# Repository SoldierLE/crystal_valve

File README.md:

# 项目说明

​	本项目以学习为目的，主要针对模拟电路设计进行学习。参考的书籍为铃木雅臣的《晶体管电路设计》。

​	本项目将会选取书本中每个章节较为重要的几个实用电路进行PCB制作及测试。

## 文件路径说明

- 01Doc

​- books

2.设计资料

​		此处存放的是学习心得以及每个章节的PCB文件，工具采用开源KICAD，摆脱版权烦恼。

3.测试资料

​		此处将会存放PCB打板回来后的电路实测数据。

4.生产资料

​		此处主要会将最后输出的BOM表和Gerber文件发布于此。并且会做一些生产过程中的问题记录。

​		需要打板的，我尽量将每次的板子都做成100mm*100mm之内的， 以便嘉立创5元打板。

## 当前进度

2020-12-18第二章放大电路------更新至PCB版初版

​		
2025-6-24学习使用vscode进行更新，并更改文件目录，准备之后都用立创EDA

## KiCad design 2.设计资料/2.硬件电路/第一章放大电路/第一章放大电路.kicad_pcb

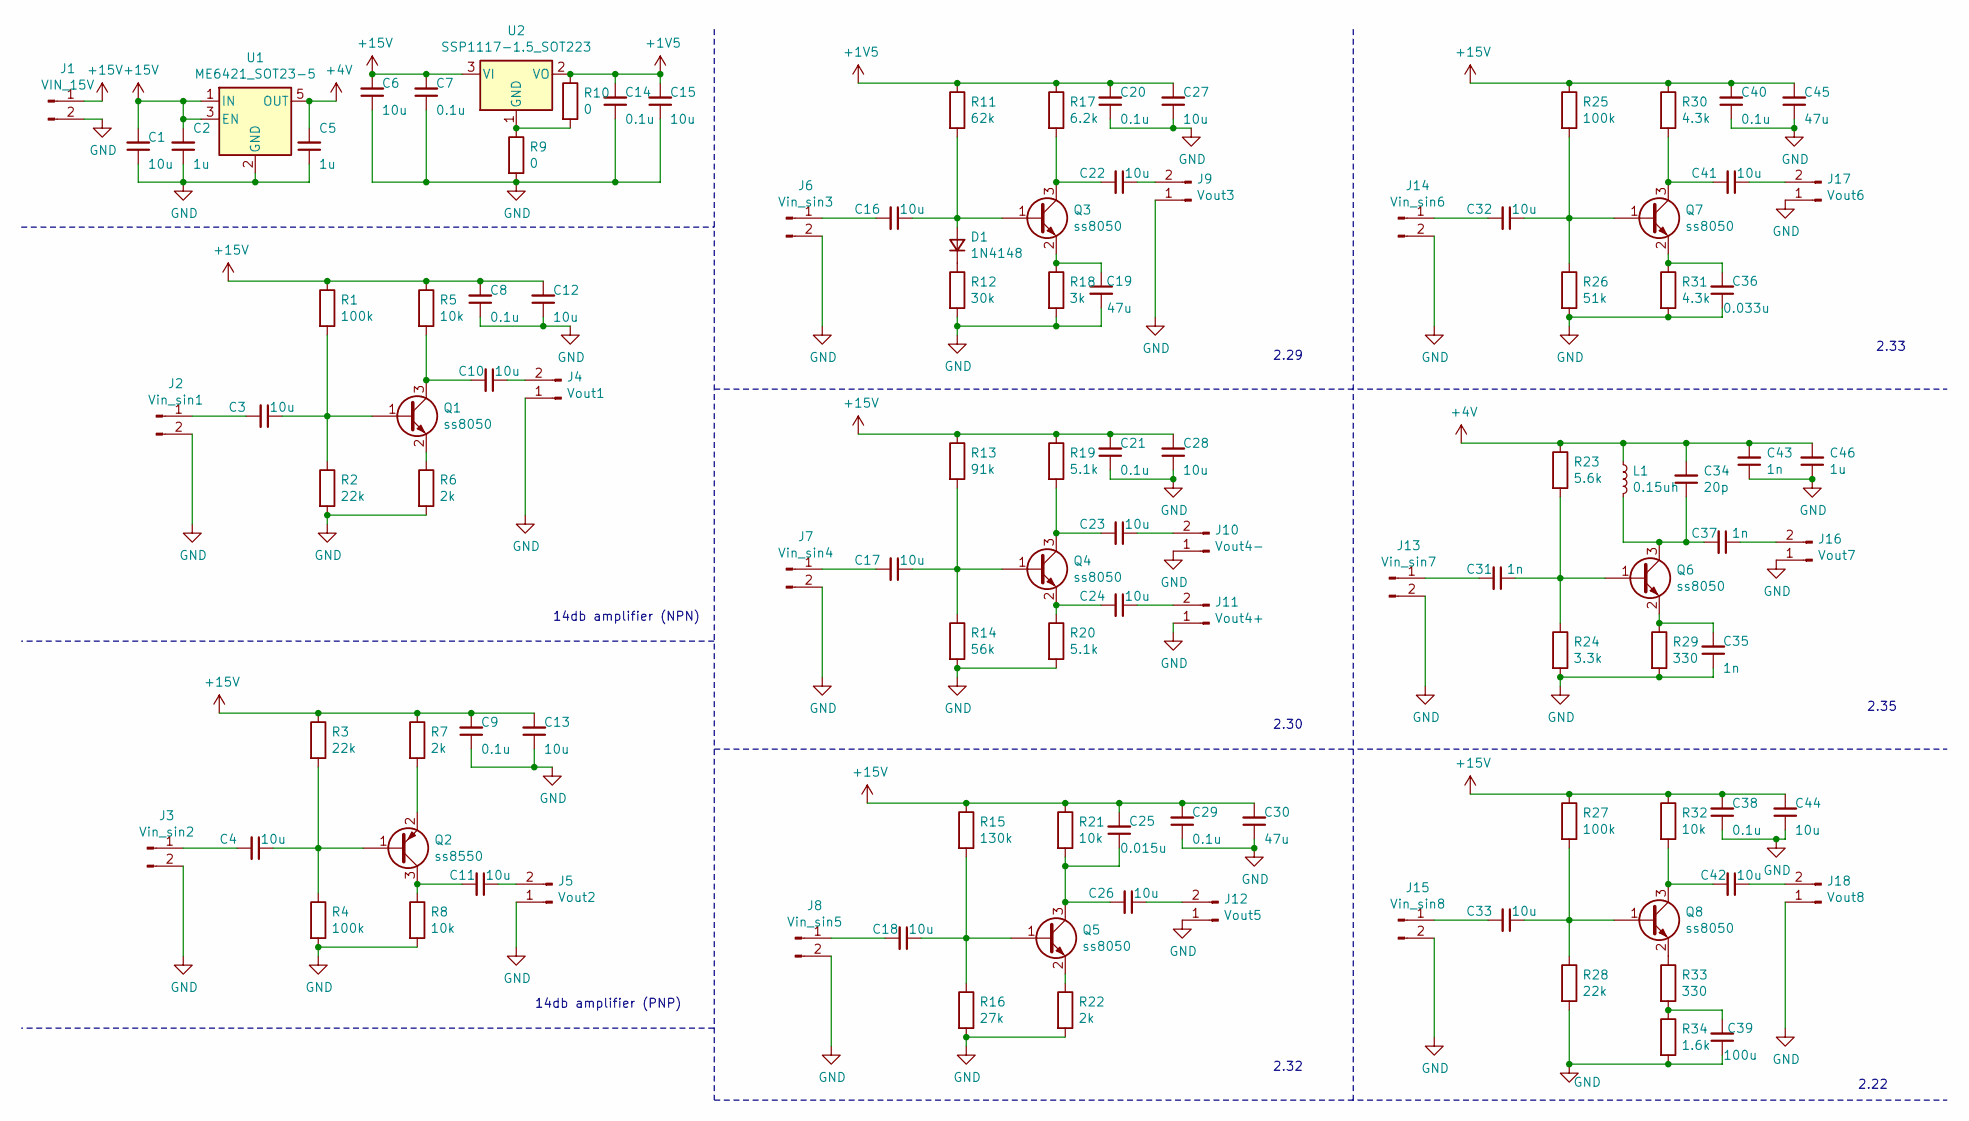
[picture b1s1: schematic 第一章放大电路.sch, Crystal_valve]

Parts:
C1, C3, C4, C6, C10, C11, C12, C13, C15, C16, C17, C18, C22, C23, C24, C26, C27, C28, C32, C33, C41, C42, C44: 10u; C_0603_1608Metric_Pad1.05x0.95mm_HandSolder
C2, C5, C46: 1u; C_0603_1608Metric_Pad1.05x0.95mm_HandSolder
C7, C8, C9, C14, C20, C21, C29, C38, C40: 0.1u; C_0603_1608Metric_Pad1.05x0.95mm_HandSolder
C19, C30, C45: 47u; C_0603_1608Metric_Pad1.05x0.95mm_HandSolder
C25: 0.015u; C_0603_1608Metric_Pad1.05x0.95mm_HandSolder
C31, C35, C37, C43: 1n; C_0603_1608Metric_Pad1.05x0.95mm_HandSolder
C34: 20p; C_0603_1608Metric_Pad1.05x0.95mm_HandSolder
C36: 0.033u; C_0603_1608Metric_Pad1.05x0.95mm_HandSolder
C39: 100u; C_0603_1608Metric_Pad1.05x0.95mm_HandSolder
D1: 1N4148; D_0603_1608Metric_Pad1.05x0.95mm_HandSolder
J1: VIN_15V; PinHeader_1x02_P2.54mm_Vertical
J2: Vin_sin1; PinHeader_1x02_P2.54mm_Vertical
J3: Vin_sin2; PinHeader_1x02_P2.54mm_Vertical
J4: Vout1; PinHeader_1x02_P2.54mm_Vertical
J5: Vout2; PinHeader_1x02_P2.54mm_Vertical
J6: Vin_sin3; PinHeader_1x02_P2.54mm_Vertical
J7: Vin_sin4; PinHeader_1x02_P2.54mm_Vertical
J8: Vin_sin5; PinHeader_1x02_P2.54mm_Vertical
J9: Vout3; PinHeader_1x02_P2.54mm_Vertical
J10: Vout4-; PinHeader_1x02_P2.54mm_Vertical
J11: Vout4+; PinHeader_1x02_P2.54mm_Vertical
J12: Vout5; PinHeader_1x02_P2.54mm_Vertical
J13: Vin_sin7; PinHeader_1x02_P2.54mm_Vertical
J14: Vin_sin6; PinHeader_1x02_P2.54mm_Vertical
J15: Vin_sin8; PinHeader_1x02_P2.54mm_Vertical
J16: Vout7; PinHeader_1x02_P2.54mm_Vertical
J17: Vout6; PinHeader_1x02_P2.54mm_Vertical
J18: Vout8; PinHeader_1x02_P2.54mm_Vertical
L1: 0.15uh; L_0603_1608Metric_Pad1.05x0.95mm_HandSolder
Q1, Q3, Q4, Q5, Q6, Q7, Q8: ss8050; SOT-23
Q2: ss8550; SOT-23
R1, R4, R25, R27: 100k; R_0603_1608Metric_Pad1.05x0.95mm_HandSolder
R2, R3, R28: 22k; R_0603_1608Metric_Pad1.05x0.95mm_HandSolder
R5, R8, R21, R32: 10k; R_0603_1608Metric_Pad1.05x0.95mm_HandSolder
R6, R7, R22: 2k; R_0603_1608Metric_Pad1.05x0.95mm_HandSolder
R9, R10: 0; R_0603_1608Metric_Pad1.05x0.95mm_HandSolder
R11: 62k; R_0603_1608Metric_Pad1.05x0.95mm_HandSolder
R12: 30k; R_0603_1608Metric_Pad1.05x0.95mm_HandSolder
R13: 91k; R_0603_1608Metric_Pad1.05x0.95mm_HandSolder
R14: 56k; R_0603_1608Metric_Pad1.05x0.95mm_HandSolder
R15: 130k; R_0603_1608Metric_Pad1.05x0.95mm_HandSolder
R16: 27k; R_0603_1608Metric_Pad1.05x0.95mm_HandSolder
R17: 6.2k; R_0603_1608Metric_Pad1.05x0.95mm_HandSolder
R18: 3k; R_0603_1608Metric_Pad1.05x0.95mm_HandSolder
R19, R20: 5.1k; R_0603_1608Metric_Pad1.05x0.95mm_HandSolder
R23: 5.6k; R_0603_1608Metric_Pad1.05x0.95mm_HandSolder
R24: 3.3k; R_0603_1608Metric_Pad1.05x0.95mm_HandSolder
R26: 51k; R_0603_1608Metric_Pad1.05x0.95mm_HandSolder
R29, R33: 330; R_0603_1608Metric_Pad1.05x0.95mm_HandSolder
R30, R31: 4.3k; R_0603_1608Metric_Pad1.05x0.95mm_HandSolder
R34: 1.6k; R_0603_1608Metric_Pad1.05x0.95mm_HandSolder
U1: ME6421_SOT23-5; SOT-23-5
U2: SSP1117-1.5_SOT223; SOT-223-3_TabPin2

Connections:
+1V5: C14.2, C15.2, C20.2, C27.2, R10.1, R11.1, R17.1, U2.2 (VO)
+4V: C5.2, C34.2, C43.2, C46.2, L1.1, R23.1, U1.5 (OUT)
+15V: C1.2, C2.2, C6.2, C7.2, C8.2, C9.2, C12.2, C13.2, C21.2, C25.2, C28.2, C29.2, C30.2, C38.2, C40.2, C44.2, C45.2, J1.1, R1.1, R3.1, R5.1, R7.1, R13.1, R15.1, R19.1, R21.1, R25.1, R27.1, R30.1, R32.1, U1.1 (IN), U1.3 (EN), U2.3 (VI)
GND: C1.1, C2.1, C5.1, C6.1, C7.1, C8.1, C9.1, C12.1, C13.1, C14.1, C15.1, C19.2, C20.1, C21.1, C27.1, C28.1, C29.1, C30.1, C35.1, C36.1, C38.1, C39.1, C40.1, C43.1, C44.1, C45.1, C46.1, J1.2, J2.2, J3.2, J4.1, J5.1, J6.2, J7.2, J8.2, J9.1, J10.1, J11.1, J12.1, J13.2, J14.2, J15.2, J16.1, J17.1, J18.1, R2.2, R4.2, R6.2, R8.2, R9.2, R12.2, R14.2, R16.2, R18.2, R20.2, R22.2, R24.2, R26.2, R28.2, R29.2, R31.2, R34.2, U1.2 (GND)
unnamed: C3.1, Q1.1 (B), R1.2, R2.1
unnamed: C3.2, J2.1
unnamed: C4.1, Q2.1 (B), R3.2, R4.1
unnamed: C4.2, J3.1
unnamed: C10.1, J4.2
unnamed: C10.2, Q1.3 (C), R5.2
unnamed: C11.1, J5.2
unnamed: C11.2, Q2.3 (C), R8.1
unnamed: C16.1, D1.2 (A), Q3.1 (B), R11.2
unnamed: C16.2, J6.1
unnamed: C17.1, Q4.1 (B), R13.2, R14.1
unnamed: C17.2, J7.1
unnamed: C18.1, Q5.1 (B), R15.2, R16.1
unnamed: C18.2, J8.1
unnamed: C19.1, Q3.2 (E), R18.1
unnamed: C22.1, J9.2
unnamed: C22.2, Q3.3 (C), R17.2
unnamed: C23.1, J10.2
unnamed: C23.2, Q4.3 (C), R19.2
unnamed: C24.1, J11.2
unnamed: C24.2, Q4.2 (E), R20.1
unnamed: C25.1, C26.2, Q5.3 (C), R21.2
unnamed: C26.1, J12.2
unnamed: C31.1, Q6.1 (B), R23.2, R24.1
unnamed: C31.2, J13.1
unnamed: C32.1, Q7.1 (B), R25.2, R26.1
unnamed: C32.2, J14.1
unnamed: C33.1, Q8.1 (B), R27.2, R28.1
unnamed: C33.2, J15.1
unnamed: C34.1, C37.2, L1.2, Q6.3 (C)
unnamed: C35.2, Q6.2 (E), R29.1
unnamed: C36.2, Q7.2 (E), R31.1
unnamed: C37.1, J16.2
unnamed: C39.2, R33.2, R34.1
unnamed: C41.1, J17.2
unnamed: C41.2, Q7.3 (C), R30.2
unnamed: C42.1, J18.2
unnamed: C42.2, Q8.3 (C), R32.2
unnamed: D1.1 (K), R12.1
unnamed: Q1.2 (E), R6.1
unnamed: Q2.2 (E), R7.2
unnamed: Q5.2 (E), R22.1
unnamed: Q8.2 (E), R33.1
unnamed: R9.1, R10.2, U2.1 (GND)

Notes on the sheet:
14db amplifier (NPN)
14db amplifier (PNP)
2.32
2.30
2.29
2.33
2.35
2.22

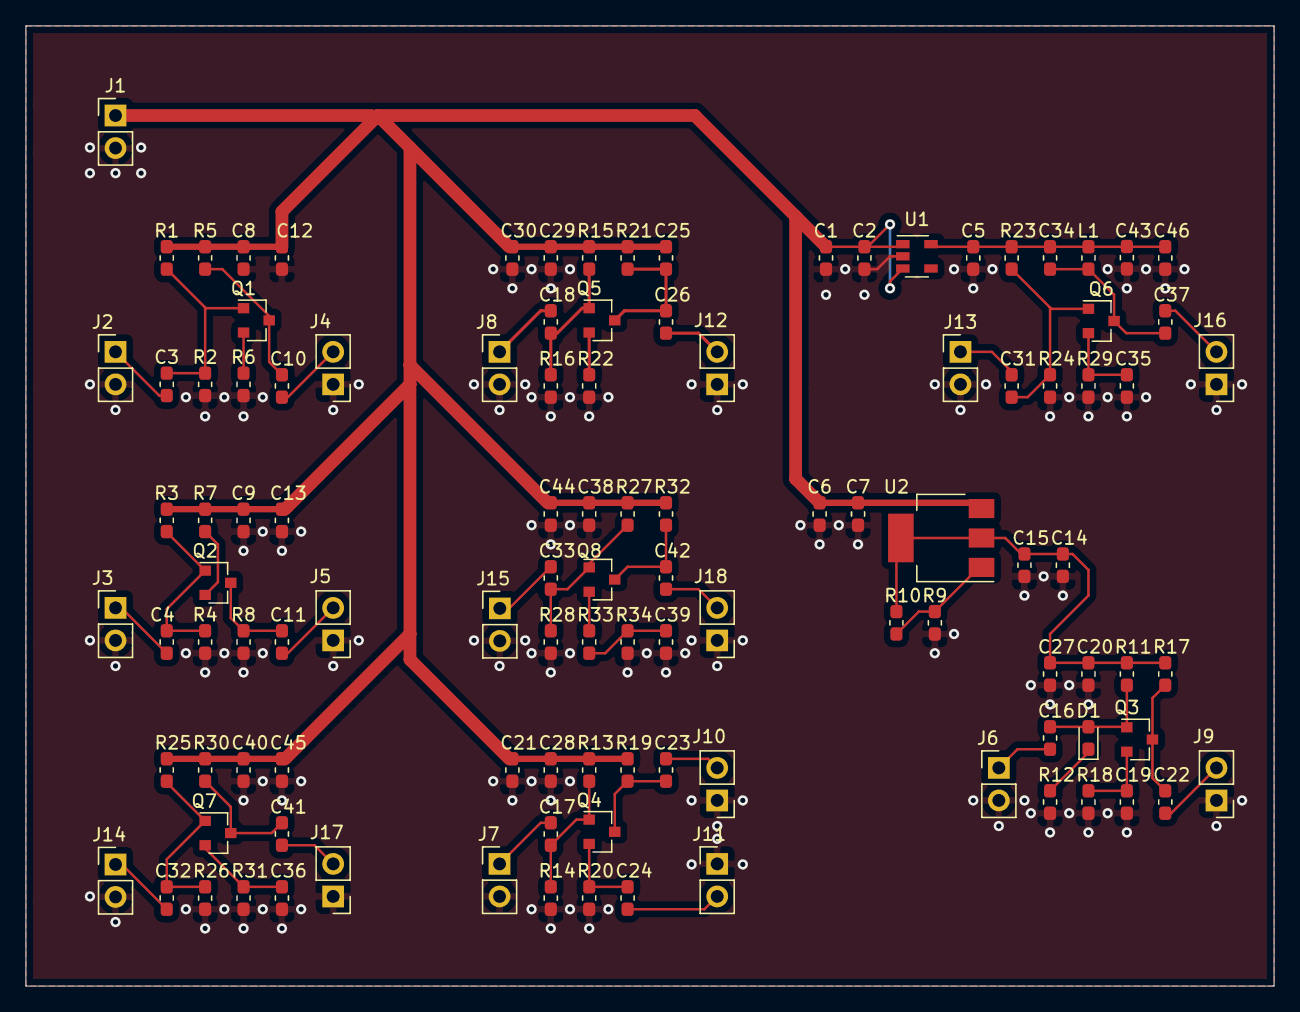
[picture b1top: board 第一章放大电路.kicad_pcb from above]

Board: 2 copper layers, 97.5 x 75.0 mm, 110 parts (0 on the bottom side), 48 nets.

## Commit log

2020-12-06 第二章电路选取，原理图制作及资料收集
2020-12-08 完成原理图绘制，并且选好期间封装
2020-12-17 PCB 布局完成
2020-12-18 PCB布板完成，并且生成gerber文件
2023-04-24 4-24update
2025-06-23 压缩一个文件夹
2025-06-23 文件结构改动
